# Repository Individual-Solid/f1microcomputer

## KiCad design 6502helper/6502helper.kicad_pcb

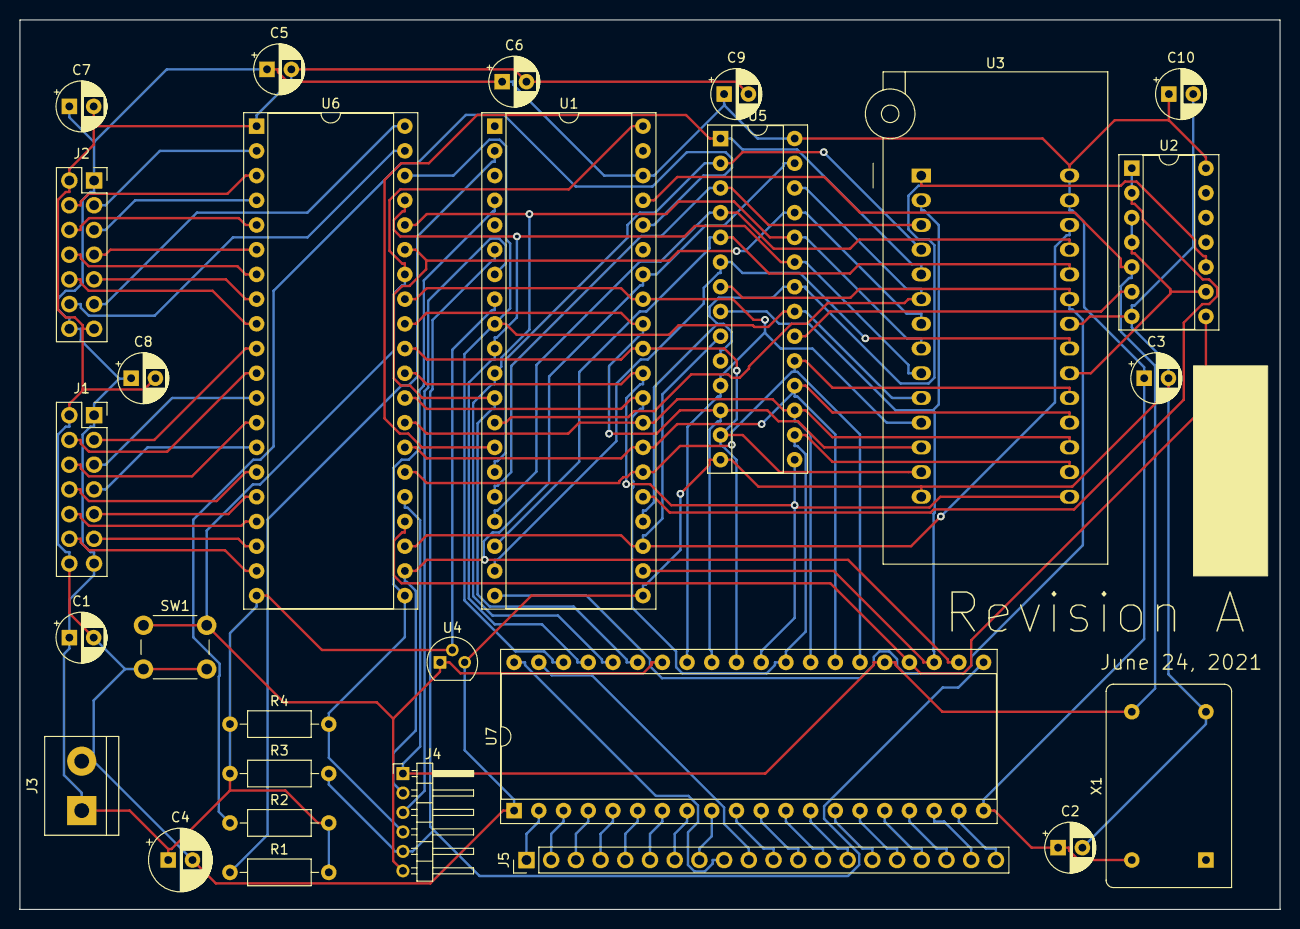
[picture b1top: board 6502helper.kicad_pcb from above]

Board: 2 copper layers, 129.5 x 91.4 mm, 28 parts (0 on the bottom side), 77 nets.

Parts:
C1, C2, C3: 0.1uF; CP_Radial_D5.0mm_P2.50mm
C4: CP1; CP_Radial_D6.3mm_P2.50mm
C5, C6, C7, C8, C9, C10: .01uF; CP_Radial_D5.0mm_P2.50mm
J1: IO Port 2; PinSocket_2x07_P2.54mm_Vertical
J2: IO Port 1; PinSocket_2x07_P2.54mm_Vertical
J3: Screw_Terminal_01x02; TerminalBlock_bornier-2_P5.08mm
J4: Control Bus Port; PinHeader_1x06_P2.00mm_Horizontal
J5: IO3; PinHeader_1x20_P2.54mm_Vertical
R1, R2, R3, R4: 3.3; R_Axial_DIN0207_L6.3mm_D2.5mm_P10.16mm_Horizontal
SW1: SW_Push; SW_PUSH_6mm_H9.5mm
U1: W65C02SxP; DIP-40_W15.24mm_Socket
U2: 74HC00; DIP-14_W7.62mm_Socket
U3: 28C256; DIP_Socket-28_W11.9_W12.7_W15.24_W17.78_W18.5_3M_228-1277-0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
U4: DS1813; TO-92
U5: CY7C199; DIP-28_W7.62mm_Socket
U6, U7: W65C22SxP; DIP-40_W15.24mm_Socket
X1: 1MHz; Oscillator_DIP-14

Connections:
+5V: C1.1, C2.1, C3.1, C4.1, C5.1, C6.1, C7.1, C8.1, C9.1, C10.1, J1.1, J1.13, J2.1, J2.14, J3.1, R1.2, R2.2, R3.1, R4.1, U1.8, U1.38, U2.14, U3.27, U3.28, U4.2, U5.28, U6.20, U7.20, X1.14
/A0: U1.9, U3.10, U5.21, U6.38, U7.38
/A1: U1.10, U3.9, U5.23, U6.37, U7.37
/A2: U1.11, U3.8, U5.24, U6.36, U7.36
/A3: U1.12, U3.7, U5.25, U6.35, U7.35
/A4: U1.13, U3.6, U5.26
/A5: U1.14, U3.5, U5.1
/A6: U1.15, U3.4, U5.2
/A7: U1.16, U3.3, U5.3
/A8: U1.17, U3.25, U5.4
/A9: U1.18, U3.24, U5.5
/A10: U1.19, U3.21, U5.6
/A11: U1.20, U3.23, U5.7
/A12: U1.22, U3.2, U5.8, U7.23
/A13: U1.23, U3.26, U5.9, U6.23
/A14: U1.24, U2.10, U3.1, U5.10, U5.22
/A15: U1.25, U2.1, U2.2
/D0: U1.33, U3.11, U5.11, U6.33, U7.33
/D1: U1.32, U3.12, U5.12, U6.32, U7.32
/D2: U1.31, U3.13, U5.13, U6.31, U7.31
/D3: U1.30, U3.15, U5.15, U6.30, U7.30
/D4: U1.29, U3.16, U5.16, U6.29, U7.29
/D5: U1.28, U3.17, U5.17, U6.28, U7.28
/D6: U1.27, U3.18, U5.18, U6.27, U7.27
/D7: U1.26, U3.19, U5.19, U6.26, U7.26
/~IOSEL~: U2.8, U6.24, U7.24
/~RAMSEL~: U2.6, U5.20
/~ROMSEL~: U2.3, U2.4, U2.9, U3.20
CLK: J4.1, U1.37, U2.5, U6.25, U7.25, X1.8
GND: C1.2, C2.2, C3.2, C4.2, C5.2, C6.2, C7.2, C8.2, C9.2, C10.2, J1.2, J1.14, J2.2, J2.13, J3.2, SW1.2, U1.21, U2.7, U3.14, U3.22, U4.3, U5.14, U6.1, U7.1, X1.7
IO0: J2.3, U6.2
IO1: J2.4, U6.3
IO2: J2.5, U6.4
IO3: J2.6, U6.5
IO4: J2.7, U6.6
IO5: J2.8, U6.7
IO6: J2.9, U6.8
IO7: J2.10, U6.9
IO8: J2.11, U6.40
IO9: J2.12, U6.39
IO10: J1.3, U6.10
IO11: J1.4, U6.11
IO12: J1.5, U6.12
IO13: J1.6, U6.13
IO14: J1.7, U6.14
IO15: J1.8, U6.15
IO16: J1.9, U6.16
IO17: J1.10, U6.17
IO18: J1.11, U6.18
IO19: J1.12, U6.19
IO20: J5.1, U7.2
IO21: J5.2, U7.3
IO22: J5.3, U7.4
IO23: J5.4, U7.5
IO24: J5.5, U7.6
IO25: J5.6, U7.7
IO26: J5.7, U7.8
IO27: J5.8, U7.9
IO28: J5.9, U7.40
IO29: J5.10, U7.39
IO30: J5.11, U7.10
IO31: J5.12, U7.11
IO32: J5.13, U7.12
IO33: J5.14, U7.13
IO34: J5.15, U7.14
IO35: J5.16, U7.15
IO36: J5.17, U7.16
IO37: J5.18, U7.17
IO38: J5.19, U7.18
IO39: J5.20, U7.19
unnamed: R1.1, U1.2
unnamed: R2.1, U1.36
R~W~: J4.2, U1.34, U5.27, U6.22, U7.22
Sync: J4.3, U1.7
~IRQ~: J4.4, R4.2, U1.4, U6.21
~NMI~: J4.5, R3.2, U1.6, U7.21
~RESET~: J4.6, SW1.1, U1.40, U4.1, U6.34, U7.34

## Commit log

2021-08-11 revision 1
2021-08-13 correct rc6502 pinout
